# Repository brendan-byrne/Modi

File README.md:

#Modi Controller Series#
Xiwi Electronics - [http://xiwielectronics.com/](http://xiwielectronics.com/)  
Brendan Byrne - [http://brendanbyrne.info](http://brendanbyrne.info)  
Assembly Instructions - [http://brendanbyrne.info/Hybri-Assembly-Instructions](http://brendanbyrne.info/Hybri-Assembly-Instructions)

**DESCRIPTION**  
Modi is a expandable controller bank system designed for AVR microcontroller platforms like Arduino and Teensy. There are four distinct module types available, each consisting of either 8 or 16 individually readable analog or digital controllers. Modi boards can be stacked to support up to 64 inputs making them ideal for MIDI/OSC projects.

**INSTALLATION**  
After downloading, move the *Modi* folder to your *Arduino Libraries* folder. Restart the Arduino IDE if already running, then open *File->Examples->Modi>allReadings* sketch.

**CLASSES AND METHODS**  
*CONSTRUCTOR*  
Modi Matrix(byte pcbA, byte pcbB, byte pcbC, byte toggleSmoothing)

- Set the arguments pcbA, pcbB, and pcbC to the pins that the Modi A, B, and C PCB pins are connected to. These can be any digital output pins.
- The toggleSmoothing argument allows you to turn a simple smoothing function on and off.
	- 0 = no smoothing
	- 1 = smooth by [Paul Badger 2007](http://tiny.cc/0db2rx) 
		- You have the option of changing the amount of smoothing. *Matrix.smoothingAmount* stores this value. .0001 indicates minimum smoothing while  .999 results in maximum smoothing. The default value is .5
 
*ATTACHING PINS*  
void Matrix.attach(byte pin, String type)

- Call this method in the setup() portion of your sketch.
- Start with the top most row. The library uses this to reference its position automatically.
- The pin argument indicates the pin the row is connected to.
- The second argument indicates the kind of row. The Modi library recognizes the following three strings: "pot", "button", and "slide".
- The numbers for signal paths on the PCB are entirely arbitary and are intended to be used to plan *electronically*.
    
*NEW READINGS*     
void Matrix.refresh()

- Call this function at the beginning of each loop to refresh readings.
  
*GET READINGS*    
int Matrix.getReading(byte row, byte column)

- Call this function to retrieve the readings from the Modi grid.
- (0, 0) is the top-left most controller 
- The Grid object supports a matrix of up to (7, 7)
- Pins marked as "buttons" will return a 0 or 1
- Pins marked as "pot" or "slide" will return values between 0 and 1023

**CONSTANTS AND ATTRIBUTES**  
*muxChannels*  
The number of channels the 4051 multiplexer supports. This constant's value is 8.

*Matrix.smoothAmount*  
When toggleSmoothing is activated this attribute determines the amount of smoothing applied to readings. .001 indicates minimum smoothing while .999 results in maximum smoothing. The default value is .5

*Matrix.numMux*  
numMux is equal to the number of times attach() is called in setup which should also be equal to the total number of multiplexers in your Modi system.

*Matrix.analogType[]*  
An array that stores whether analogRead() or digitalRead() is to be used when collecting readings. This attribute comes in handy when utilizing different commands with different controller types. In the case of  the midiOut example sketch contained within this library, the attribute is used to send some readings as Note On/Off messages and others as CC messages. 0 = digital and 1 = analog

**OPEN SOURCE**  
Modi is an Open-Source Hardware 1.0 Project

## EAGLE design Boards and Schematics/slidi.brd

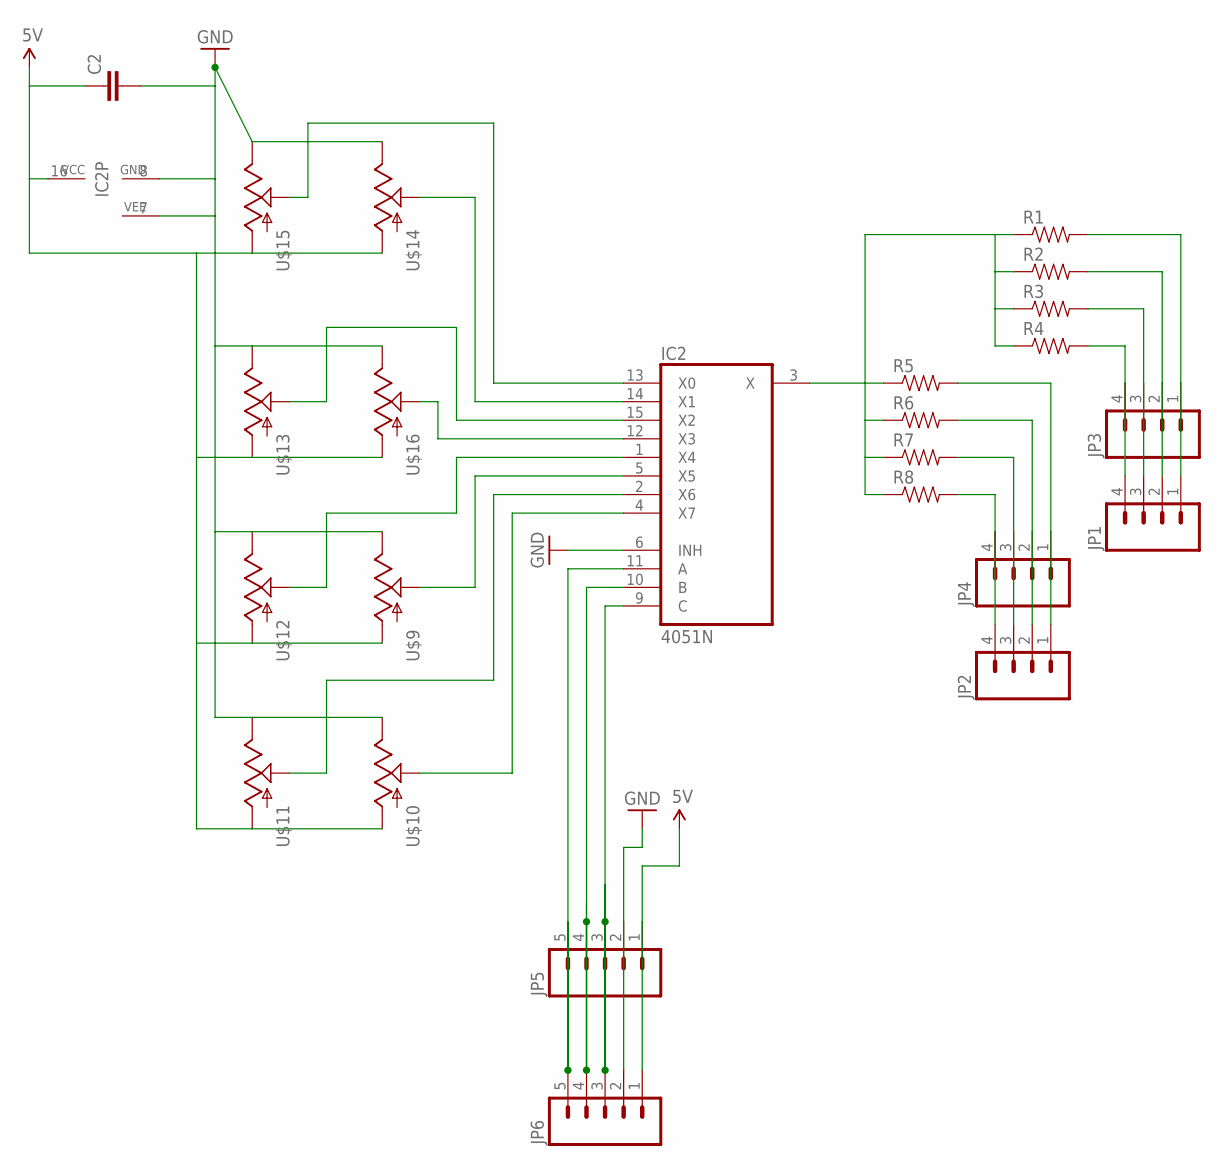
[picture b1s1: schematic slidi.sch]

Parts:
C2: CAPPTH; CAP-PTH-SMALL
IC2: 4051N; DIL16
JP1, JP2, JP3, JP4: M04PTH; 1X04
JP5, JP6: M05PTH; 1X05
R1, R2, R3, R4, R5, R6, R7, R8: RESISTORAXIAL-0.3; AXIAL-0.3
U$9, U$10, U$11, U$12, U$13, U$14, U$15, U$16: SLIDEPOT

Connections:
5V: C2.1, IC2.16 (VCC), JP5.1, JP6.1, U$9.GND (A), U$10.GND (A), U$11.GND (A), U$12.GND (A), U$13.GND (A), U$14.GND (A), U$15.GND (A), U$16.GND (A)
GND: C2.2, IC2.6 (INH), IC2.7 (VEE), IC2.8 (GND), JP5.2, JP6.2, U$9.5V (E), U$10.5V (E), U$11.5V (E), U$12.5V (E), U$13.5V (E), U$14.5V (E), U$15.5V (E), U$16.5V (E)
unnamed: IC2.14 (X1), U$14.WIPER (S)
unnamed: IC2.13 (X0), U$15.WIPER (S)
unnamed: IC2.15 (X2), U$13.WIPER (S)
unnamed: IC2.12 (X3), U$16.WIPER (S)
unnamed: IC2.1 (X4), U$12.WIPER (S)
unnamed: IC2.5 (X5), U$9.WIPER (S)
unnamed: IC2.2 (X6), U$11.WIPER (S)
unnamed: IC2.4 (X7), U$10.WIPER (S)
unnamed: IC2.3 (X), R1.P$1 (1), R2.P$1 (1), R3.P$1 (1), R4.P$1 (1), R5.P$1 (1), R6.P$1 (1), R7.P$1 (1), R8.P$1 (1)
unnamed: IC2.10 (B), JP5.4, JP6.4
unnamed: IC2.11 (A), JP5.5, JP6.5
unnamed: IC2.9 (C), JP5.3, JP6.3
unnamed: JP1.4, JP3.4, R4.P$2 (2)
unnamed: JP1.3, JP3.3, R3.P$2 (2)
unnamed: JP1.2, JP3.2, R2.P$2 (2)
unnamed: JP1.1, JP3.1, R1.P$2 (2)
unnamed: JP2.4, JP4.4, R8.P$2 (2)
unnamed: JP2.3, JP4.3, R7.P$2 (2)
unnamed: JP2.2, JP4.2, R6.P$2 (2)
unnamed: JP2.1, JP4.1, R5.P$2 (2)

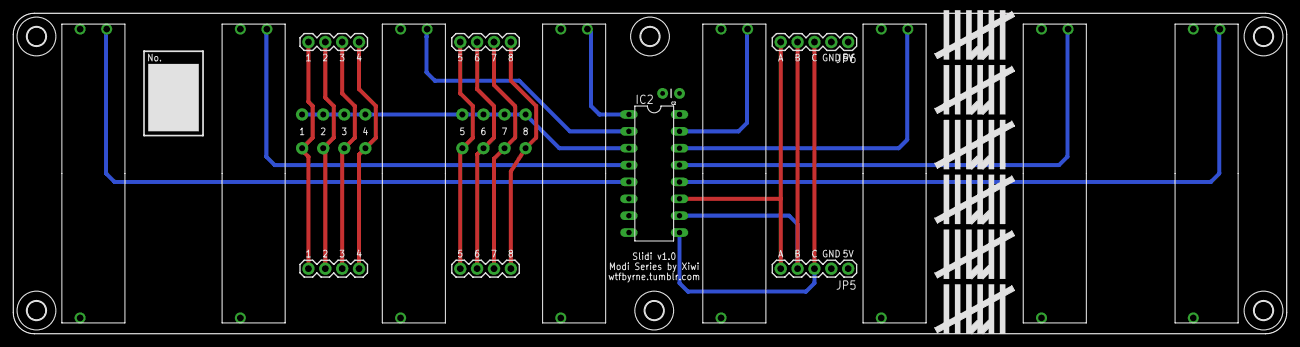
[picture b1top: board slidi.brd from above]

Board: 2 copper layers, 191.8 x 48.3 mm, 36 parts (0 on the bottom side), 22 nets.

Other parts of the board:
U$17, U$18, U$19, U$20, U$21, U$22: 2,8
U$23, U$24, U$25, U$26, U$27, U$28: XIWI

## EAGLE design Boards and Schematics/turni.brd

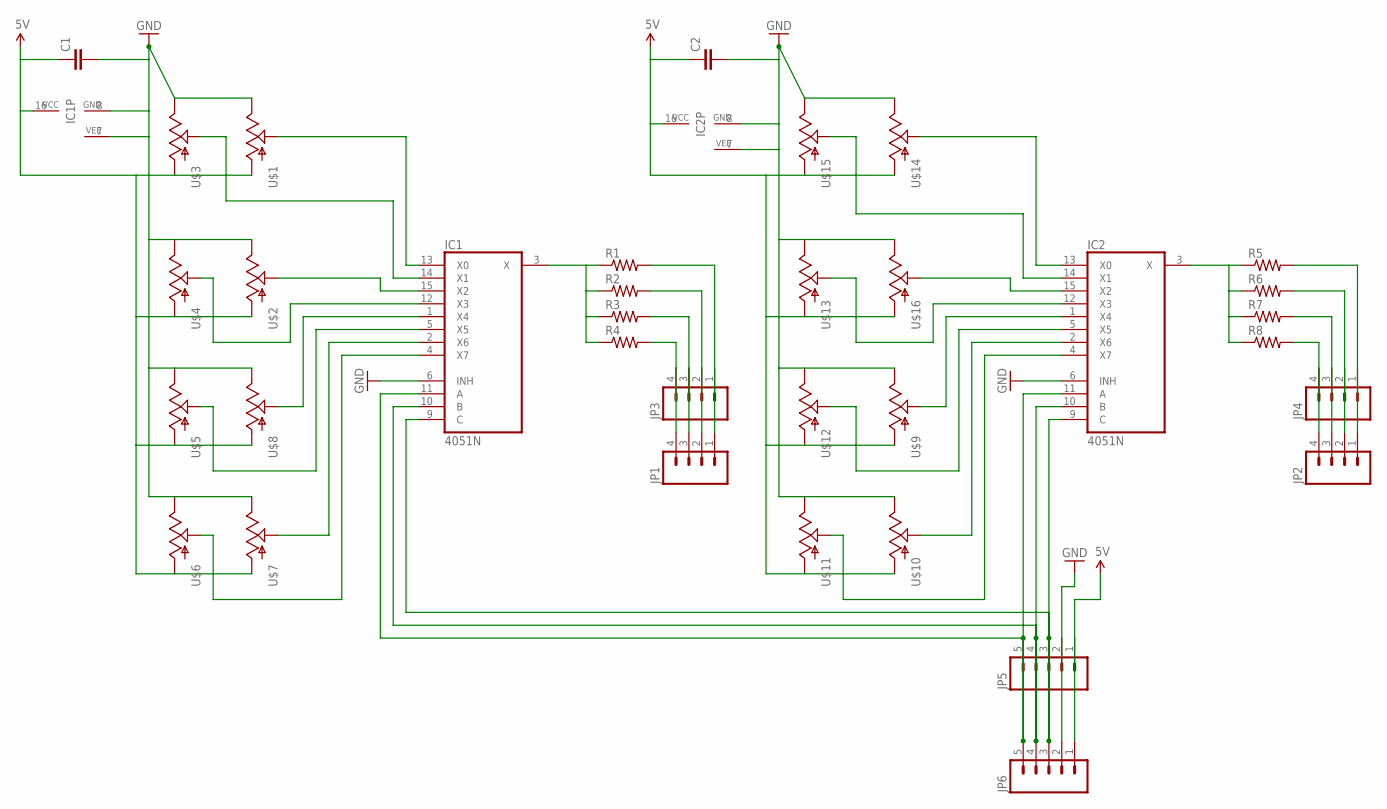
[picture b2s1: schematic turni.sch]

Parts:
C1, C2: CAPPTH; CAP-PTH-SMALL
IC1, IC2: 4051N; DIL16
JP1, JP2, JP3, JP4: M04PTH; 1X04
JP5, JP6: M05PTH; 1X05
R1, R2, R3, R4, R5, R6, R7, R8: RESISTORAXIAL-0.3; AXIAL-0.3
U$1, U$2, U$3, U$4, U$5, U$6, U$7, U$8, U$9, U$10, U$11, U$12, U$13, U$14, U$15, U$16: POT; ALPS_POT

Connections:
5V: C1.1, C2.1, IC1.16 (VCC), IC2.16 (VCC), JP5.1, JP6.1, U$1.P$3 (A), U$2.P$3 (A), U$3.P$3 (A), U$4.P$3 (A), U$5.P$3 (A), U$6.P$3 (A), U$7.P$3 (A), U$8.P$3 (A), U$9.P$3 (A), U$10.P$3 (A), U$11.P$3 (A), U$12.P$3 (A), U$13.P$3 (A), U$14.P$3 (A), U$15.P$3 (A), U$16.P$3 (A)
GND: C1.2, C2.2, IC1.6 (INH), IC1.7 (VEE), IC1.8 (GND), IC2.6 (INH), IC2.7 (VEE), IC2.8 (GND), JP5.2, JP6.2, U$1.P$1 (E), U$2.P$1 (E), U$3.P$1 (E), U$4.P$1 (E), U$5.P$1 (E), U$6.P$1 (E), U$7.P$1 (E), U$8.P$1 (E), U$9.P$1 (E), U$10.P$1 (E), U$11.P$1 (E), U$12.P$1 (E), U$13.P$1 (E), U$14.P$1 (E), U$15.P$1 (E), U$16.P$1 (E)
unnamed: IC1.13 (X0), U$1.P$2 (S)
unnamed: IC1.14 (X1), U$3.P$2 (S)
unnamed: IC1.15 (X2), U$2.P$2 (S)
unnamed: IC1.12 (X3), U$4.P$2 (S)
unnamed: IC1.1 (X4), U$8.P$2 (S)
unnamed: IC1.5 (X5), U$5.P$2 (S)
unnamed: IC1.2 (X6), U$7.P$2 (S)
unnamed: IC1.4 (X7), U$6.P$2 (S)
unnamed: IC2.13 (X0), U$14.P$2 (S)
unnamed: IC2.14 (X1), U$15.P$2 (S)
unnamed: IC2.15 (X2), U$16.P$2 (S)
unnamed: IC2.12 (X3), U$13.P$2 (S)
unnamed: IC2.1 (X4), U$9.P$2 (S)
unnamed: IC2.5 (X5), U$12.P$2 (S)
unnamed: IC2.2 (X6), U$10.P$2 (S)
unnamed: IC2.4 (X7), U$11.P$2 (S)
unnamed: IC1.3 (X), R1.P$1 (1), R2.P$1 (1), R3.P$1 (1), R4.P$1 (1)
unnamed: IC1.10 (B), IC2.10 (B), JP5.4, JP6.4
unnamed: IC1.11 (A), IC2.11 (A), JP5.5, JP6.5
unnamed: IC1.9 (C), IC2.9 (C), JP5.3, JP6.3
unnamed: JP1.4, JP3.4, R4.P$2 (2)
unnamed: JP1.3, JP3.3, R3.P$2 (2)
unnamed: JP1.2, JP3.2, R2.P$2 (2)
unnamed: JP1.1, JP3.1, R1.P$2 (2)
unnamed: IC2.3 (X), R5.P$1 (1), R6.P$1 (1), R7.P$1 (1), R8.P$1 (1)
unnamed: JP2.4, JP4.4, R8.P$2 (2)
unnamed: JP2.3, JP4.3, R7.P$2 (2)
unnamed: JP2.2, JP4.2, R6.P$2 (2)
unnamed: JP2.1, JP4.1, R5.P$2 (2)

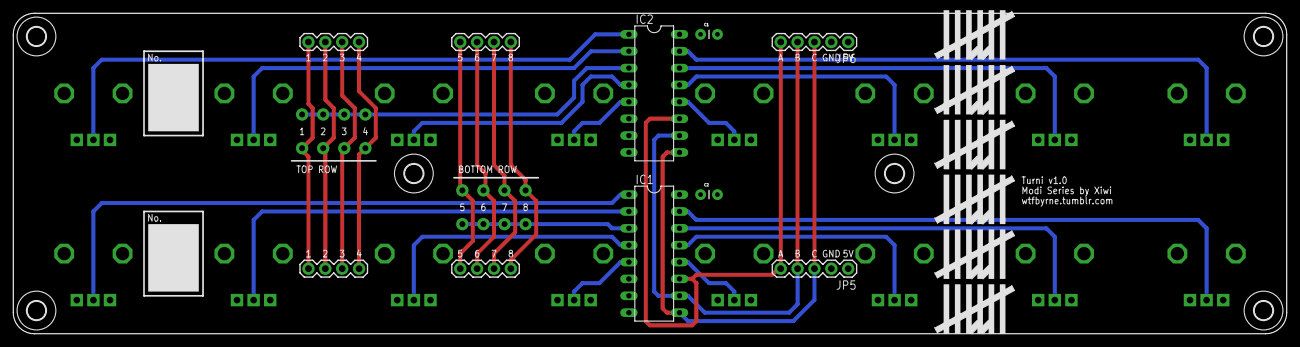
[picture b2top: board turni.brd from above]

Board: 2 copper layers, 191.8 x 48.3 mm, 46 parts (0 on the bottom side), 31 nets.

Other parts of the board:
U$17, U$18, U$19, U$20, U$21, U$22: 2,8
U$23, U$24, U$25, U$26, U$27, U$28: XIWI

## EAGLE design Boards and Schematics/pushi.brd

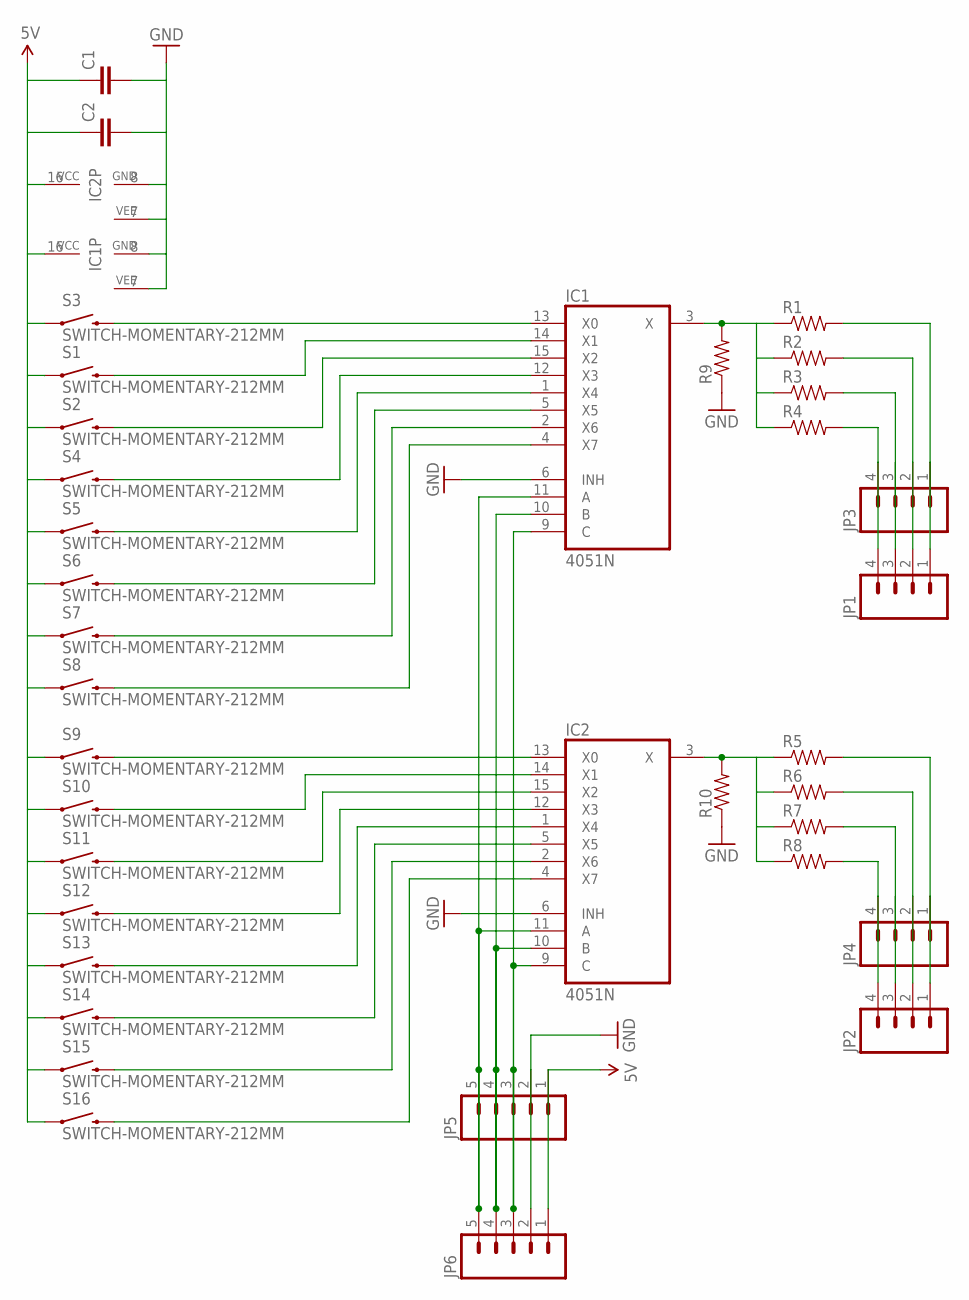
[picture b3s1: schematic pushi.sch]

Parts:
C1, C2: CAPPTH; CAP-PTH-SMALL
IC1, IC2: 4051N; DIL16
JP1, JP2, JP3, JP4: M04PTH; 1X04
JP5, JP6: M05PTH; 1X05
R1, R2, R3, R4, R5, R6, R7, R8, R9, R10: RESISTORAXIAL-0.3; AXIAL-0.3
S1, S2, S3, S4, S5, S6, S7, S8, S9, S10, S11, S12, S13, S14, S15, S16: SWITCH-MOMENTARY-212MM; TACTILE-PTH-12MM

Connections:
5V: C1.1, C2.1, IC1.16 (VCC), IC2.16 (VCC), JP5.1, JP6.1, S1.1, S2.1, S3.1, S4.1, S5.1, S6.1, S7.1, S8.1, S9.1, S10.1, S11.1, S12.1, S13.1, S14.1, S15.1, S16.1
GND: C1.2, C2.2, IC1.6 (INH), IC1.7 (VEE), IC1.8 (GND), IC2.6 (INH), IC2.7 (VEE), IC2.8 (GND), JP5.2, JP6.2, R9.P$1 (1), R10.P$1 (1)
unnamed: IC1.15 (X2), S2.3 (2)
unnamed: IC1.14 (X1), S1.3 (2)
unnamed: IC1.12 (X3), S4.3 (2)
unnamed: IC1.1 (X4), S5.3 (2)
unnamed: IC1.5 (X5), S6.3 (2)
unnamed: IC1.2 (X6), S7.3 (2)
unnamed: IC1.4 (X7), S8.3 (2)
unnamed: IC2.13 (X0), S9.3 (2)
unnamed: IC2.14 (X1), S10.3 (2)
unnamed: IC2.15 (X2), S11.3 (2)
unnamed: IC2.12 (X3), S12.3 (2)
unnamed: IC2.1 (X4), S13.3 (2)
unnamed: IC2.5 (X5), S14.3 (2)
unnamed: IC2.2 (X6), S15.3 (2)
unnamed: IC2.4 (X7), S16.3 (2)
unnamed: IC1.3 (X), R1.P$1 (1), R2.P$1 (1), R3.P$1 (1), R4.P$1 (1), R9.P$2 (2)
unnamed: IC1.10 (B), IC2.10 (B), JP5.4, JP6.4
unnamed: IC1.11 (A), IC2.11 (A), JP5.5, JP6.5
unnamed: IC1.9 (C), IC2.9 (C), JP5.3, JP6.3
unnamed: JP1.4, JP3.4, R4.P$2 (2)
unnamed: JP1.3, JP3.3, R3.P$2 (2)
unnamed: JP1.2, JP3.2, R2.P$2 (2)
unnamed: JP1.1, JP3.1, R1.P$2 (2)
unnamed: IC2.3 (X), R5.P$1 (1), R6.P$1 (1), R7.P$1 (1), R8.P$1 (1), R10.P$2 (2)
unnamed: JP2.4, JP4.4, R8.P$2 (2)
unnamed: JP2.3, JP4.3, R7.P$2 (2)
unnamed: JP2.2, JP4.2, R6.P$2 (2)
unnamed: JP2.1, JP4.1, R5.P$2 (2)
unnamed: IC1.13 (X0), S3.3 (2)

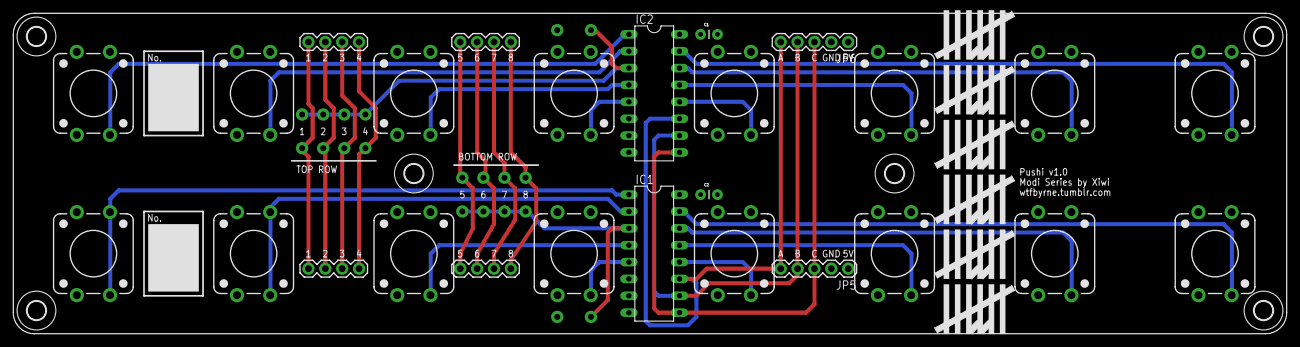
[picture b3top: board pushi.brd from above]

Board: 2 copper layers, 191.8 x 48.3 mm, 48 parts (0 on the bottom side), 31 nets.

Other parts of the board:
U$17, U$18, U$19, U$20, U$21, U$22: 2,8
U$23, U$24, U$25, U$26, U$27, U$28: XIWI

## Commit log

2015-01-07 :tada: Added .gitattributes & .gitignore files
2015-01-07 Instructions and README Uploaded
2015-01-07 Firmware Testing
2015-08-23 Big Update
2016-01-04 Fixed digitalWrite call so the correct pins get selected

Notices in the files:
parts and their libraries:
SparkFun-Electromechanical: Licensing: CC v3.0 Share-Alike You are welcome to use this library for commercial purposes.
